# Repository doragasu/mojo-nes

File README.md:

# mojo-nes

NES cartridge with no mapper support. Initially created to host homebrew projects from the infamous [THE MOJON-TWINS](http://www.mojontwins.com/), and some more from [1985alternativo](http://www.fasebonus.net/1985alternativo/).

## License
mojo-nes is licensed under the [CERN OHL 1.2](http://www.ohwr.org/licenses/cern-ohl/v1.2) license. You are free to study, distribute and make modifications to the Documentation, under the aforementioned license terms. You are also free to make cartridges derived from the Documentation for non-commercial purposes. If you want to make a commercial Product using this Documentation, please contact me to obtain a licence.

## About CAD files
CAD design files are for KiCAD Open Source electronics design suite. Please install latest version along with KiCAD libraries to open it. When opening schematic, KiCAD will most likely complain about missing library "doragasu". Despite this warning, the schematic should load nicely (using the cached libraries). To avoid this message, install [the missing library](https://github.com/doragasu/doragasu-kicad-lib) and make sure to configure it in the schematic editor.

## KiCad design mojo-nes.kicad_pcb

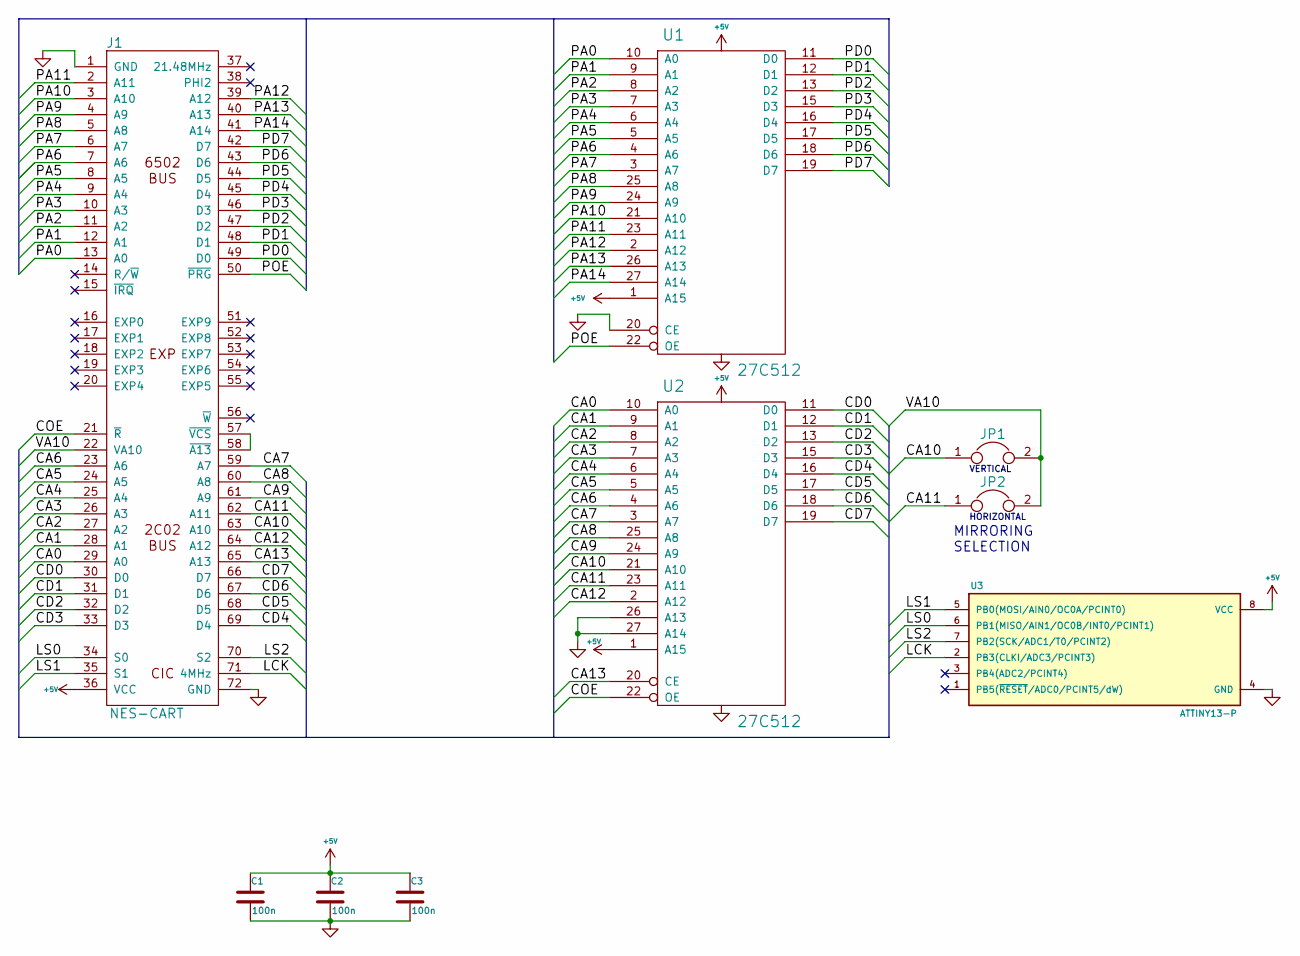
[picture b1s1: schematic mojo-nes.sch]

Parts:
C1, C2, C3: 100n; C_0805
J1: NES-CART; NES_CART_FINGERS
JP1, JP2: JUMPER; JUMPER_0805
U1, U2: 27C512; DIP-28__600
U3: ATTINY13-P; DIP-8__300

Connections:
+5V: C1.1, C2.1, C3.1, J1.36 (VCC), U1.1 (A15), U1.28 (VCC), U2.1 (A15), U2.28 (VCC), U3.8 (VCC)
/CA0: J1.29 (A0), U2.10 (A0)
/CA1: J1.28 (A1), U2.9 (A1)
/CA2: J1.27 (A2), U2.8 (A2)
/CA3: J1.26 (A3), U2.7 (A3)
/CA4: J1.25 (A4), U2.6 (A4)
/CA5: J1.24 (A5), U2.5 (A5)
/CA6: J1.23 (A6), U2.4 (A6)
/CA7: J1.59 (A7), U2.3 (A7)
/CA8: J1.60 (A8), U2.25 (A8)
/CA9: J1.61 (A9), U2.24 (A9)
/CA10: J1.63 (A10), JP1.1, U2.21 (A10)
/CA11: J1.62 (A11), JP2.1, U2.23 (A11)
/CA12: J1.64 (A12), U2.2 (A12)
/CA13: J1.65 (A13), U2.20 (CE)
/CD0: J1.30 (D0), U2.11 (D0)
/CD1: J1.31 (D1), U2.12 (D1)
/CD2: J1.32 (D2), U2.13 (D2)
/CD3: J1.33 (D3), U2.15 (D3)
/CD4: J1.69 (D4), U2.16 (D4)
/CD5: J1.68 (D5), U2.17 (D5)
/CD6: J1.67 (D6), U2.18 (D6)
/CD7: J1.66 (D7), U2.19 (D7)
/COE: J1.21 (~R), U2.22 (OE)
/LCK: J1.71 (4MHz), U3.2 (PB3(CLKI/ADC3/PCINT3))
/LS0: J1.34 (S0), U3.6 (PB1(MISO/AIN1/OC0B/INT0/PCINT1))
/LS1: J1.35 (S1), U3.5 (PB0(MOSI/AIN0/OC0A/PCINT0))
/LS2: J1.70 (S2), U3.7 (PB2(SCK/ADC1/T0/PCINT2))
/PA0: J1.13 (A0), U1.10 (A0)
/PA1: J1.12 (A1), U1.9 (A1)
/PA2: J1.11 (A2), U1.8 (A2)
/PA3: J1.10 (A3), U1.7 (A3)
/PA4: J1.9 (A4), U1.6 (A4)
/PA5: J1.8 (A5), U1.5 (A5)
/PA6: J1.7 (A6), U1.4 (A6)
/PA7: J1.6 (A7), U1.3 (A7)
/PA8: J1.5 (A8), U1.25 (A8)
/PA9: J1.4 (A9), U1.24 (A9)
/PA10: J1.3 (A10), U1.21 (A10)
/PA11: J1.2 (A11), U1.23 (A11)
/PA12: J1.39 (A12), U1.2 (A12)
/PA13: J1.40 (A13), U1.26 (A13)
/PA14: J1.41 (A14), U1.27 (A14)
/PD0: J1.49 (D0), U1.11 (D0)
/PD1: J1.48 (D1), U1.12 (D1)
/PD2: J1.47 (D2), U1.13 (D2)
/PD3: J1.46 (D3), U1.15 (D3)
/PD4: J1.45 (D4), U1.16 (D4)
/PD5: J1.44 (D5), U1.17 (D5)
/PD6: J1.43 (D6), U1.18 (D6)
/PD7: J1.42 (D7), U1.19 (D7)
/POE: J1.50 (~PRG), U1.22 (OE)
/VA10: J1.22 (VA10), JP1.2, JP2.2
GND: C1.2, C2.2, C3.2, J1.1 (GND), J1.72 (GND), U1.14 (GND), U1.20 (CE), U2.14 (GND), U2.26 (A13), U2.27 (A14), U3.4 (GND)
unnamed: J1.57 (~VCS), J1.58 (~A13)

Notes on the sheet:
VERTICAL
HORIZONTAL
MIRRORING SELECTION

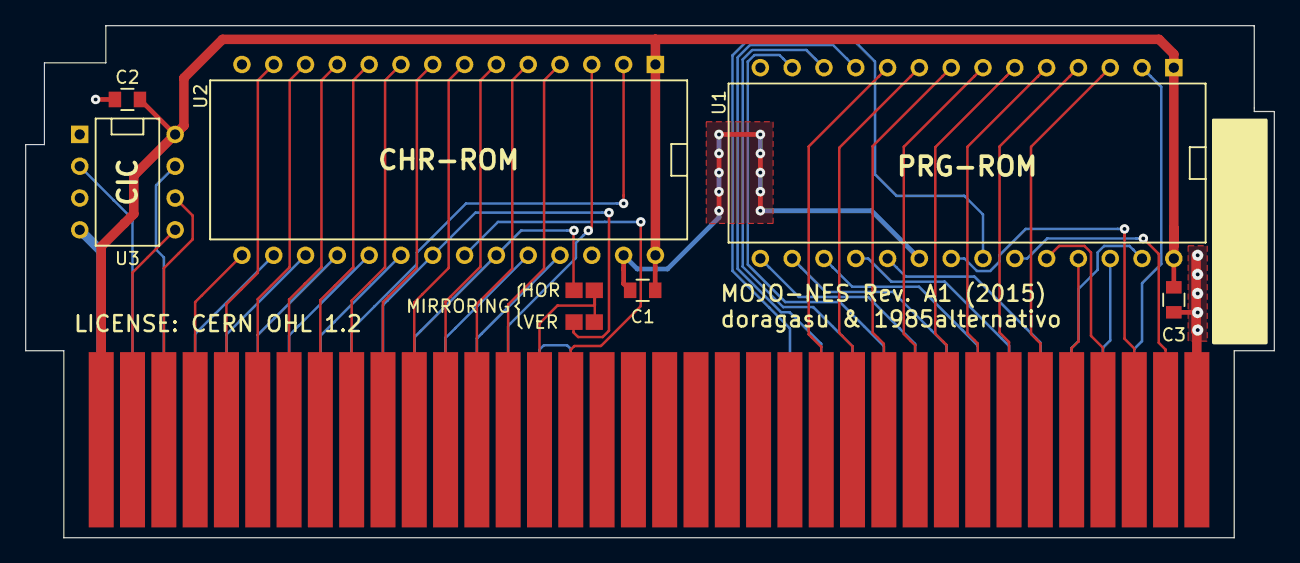
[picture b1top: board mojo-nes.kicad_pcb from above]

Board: 2 copper layers, 99.7 x 40.9 mm, 9 parts (0 on the bottom side), 55 nets.

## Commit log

2016-12-28 Added design files.
2016-12-28 Added 3D footprints and PCB render.
2016-12-28 Updated PCB render.

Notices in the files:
mojo-nes.kicad_pcb:
(licence required for product manufacture, see section 4 of License)
License: CERN OHL 1.2: http://www.ohwr.org/licenses/cern-ohl/v1.2
